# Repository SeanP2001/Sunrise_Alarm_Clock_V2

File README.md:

# Sunrise Alarm Clock V2

## Table of Contents

* [Introduction](#introduction)
* [Brief](#brief)
* [Method of Operation](#method-of-operation)
  + [Setup](#setup)
  + [Main Screen](#main-screen)
  + [Menu Layout](#menu-layout)
* [Circuitry](#circuitry)
  + [Schematic](#schematic)
  + [PCB Design](#pcb-design)
* [Enclosure](#enclosure)
  + [CAD Enclosure](#cad-enclosure)
  + [3D Printed Enclosure](#3d-printed-enclosure)
* [Demonstration](#demonstration)
* [Further Work](#further-work)

## Introduction

In my first year of university, I made a sunrise alarm clock for an assignment. Version 1 was a simple project using an Arduino Mega and an LCD keypad shield. [Here](https://github.com/SeanP2001/Arduino_Sunrise_Alarm_Clock) is a link to the repo for the original project. Over the past year and a half, I have developed my skills, so I decided to revisit this project.

## Brief

I wanted to design an alarm clock that uses light to wake me up naturally, making me feel more rested. However, I also needed an audio alarm to prevent me from solely relying on waking up naturally. Another feature I wanted to add was USB ports that could be switched on at time X and off at time Y. This would allow me to control USB-powered peripherals like lights, fans or a radio. I could also use these ports to charge devices without leaving them on charge all night.

## Method of Operation

### Setup

Before programming the alarm, you must put your Wi-Fi credentials in the "WifiCredentials.h" file.

```arduino
//------------------------ W I F I   C R E D E N T I A L S ------------------------

const char *ssid     = "YOUR_WIFI_SSID";        // REPLACE WITH YOUR WIFI SSID
const char *password = "YOUR_WIFI_PASSWORD";    // REPLACE WITH YOUR WIFI PASSWORD
```

When the alarm is first powered on, it will connect to your Wi-Fi to get the current date and time. It will then load any settings from EEPROM before it advances to the main screen (shown below).

### Main Screen

The alarm displays the day of the week and the current time on the main screen. There are also three icons. Unfortunately, the icons do not show up well in photos.

Pressing the left button will toggle the light bar on and off. When the light bar is on, the icon on the left (light bulb) changes to show it is on. When it is on, the bulb is shaded in, and when it is off, the icon is just an outline of a bulb. The light is a useful feature to help you see when you are getting into bed in the dark.

Pressing the middle button enables and disables the audio alarm. Pressing this button will cause the central icon (a bell) to change from being shaded in when the buzzer is enabled to an outline when it is disabled. If the alarm sounds, pressing the middle button will turn it off.

Pressing the right button enters the menu (shown below).

### Menu Layout

The menu has the following layout:

```
Main Menu
├── Alarm
│   ├── Light Bar
│   │   ├── On Time
│   │   └── Off Time
│   └── Buzzer
│       ├── On Time
│       └── Off Time
├── USB Ports
│   ├── USB 1
│   │   ├── On Time
│   │   └── Off Time
│   ├── USB 2
│   │   ├── On Time
│   │   └── Off Time
│   └── USB 3
│       ├── On Time
│       └── Off Time
├── Time
│   ├── Time Offset (hrs)
│   ├── Hours Between Syncs
│   └── Sync Time Now
└── Save
```

The "Alarm" settings allow you to alter when the light bar and buzzer automatically turn on and off. The "USB Ports" settings adjust when each port turns on and off.

In the "Time" menu, the "Time Offset" option allows you to set how many hours your time zone is ahead or behind UTC. The "Hours Between Syncs" option allows you to set how many hours the clock will run before it syncs to the time server again. "Sync Time Now" causes the alarm to reconnect to the Wi-Fi and connect to the time server to get the current time. This option is helpful if you have just altered the time offset and want to update the clock.

The "Save" option saves all of the settings to the EEPROM. This means you will not lose your settings when you turn the alarm off and back on again.

## Circuitry

### Schematic

### PCB Design

|  |  |
| -------------------------------------------------- | ------------------------------------------------------- |
|                |                      |

## Enclosure

### CAD Enclosure

|  |  |
| ---------------------------------------------------------------------- | ------------------------------------------------------------ |

### 3D Printed Enclosure

|  |  |  |
| ------------------------------------- | ------------------------------------------ | -------------------------------------- |

## Demonstration

## Further Work

In future, I could;

- Create other wireless modules with which the alarm can communicate (windowsill light sensor, curtain motor, lamp).
- Add a weather icon to the main screen.
- Change the design to a more traditional alarm clock shape.
- Add a puzzle to switch off the alarm. This would prevent you from just hitting snooze.

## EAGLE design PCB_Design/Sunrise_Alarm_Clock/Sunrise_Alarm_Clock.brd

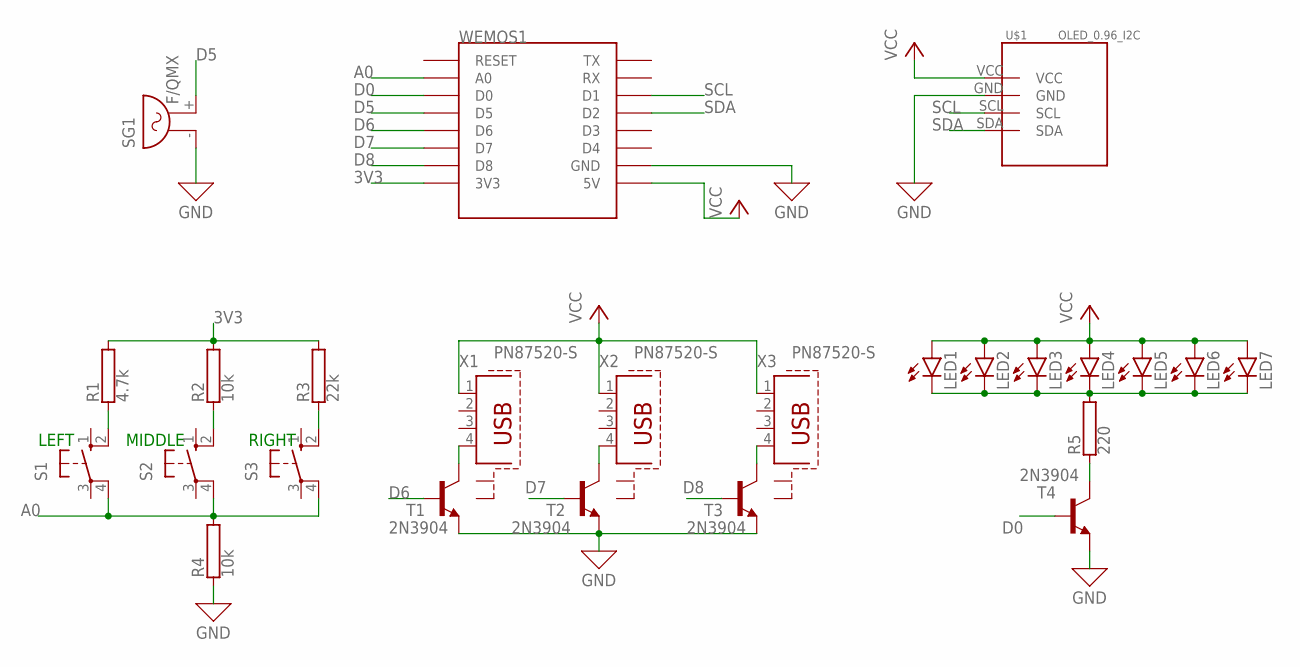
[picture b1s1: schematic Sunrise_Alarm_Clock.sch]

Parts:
LED1, LED2, LED3, LED4, LED5, LED6, LED7: LED5MM
R1: 4.7k; AC01
R2, R4: 10k; AC01
R3: 22k; AC01
R5: 220; AC01
S1, S2, S3: 10-XX; B3F-10XX
SG1: F/QMX
T1, T2, T3, T4: 2N3904; TO92
U$1: OLED_0.96_I2C
WEMOS1: WEMOS-D1-MINI
X1, X2, X3: PN87520-S

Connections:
3V3: R1.2, R2.2, R3.2, WEMOS1.3V3
A0: R4.2, S1.4 (P1), S2.4 (P1), S3.4 (P1), WEMOS1.A0
D0: T4.2 (B), WEMOS1.D0
D5: SG1.+ (2), WEMOS1.D5
D6: T1.2 (B), WEMOS1.D6
D7: T2.2 (B), WEMOS1.D7
D8: T3.2 (B), WEMOS1.D8
GND: R4.1, SG1.- (1), T1.3 (E), T2.3 (E), T3.3 (E), T4.3 (E), U$1.GND, WEMOS1.GND
unnamed: T3.1 (C), X3.4
unnamed: T2.1 (C), X2.4
unnamed: T1.1 (C), X1.4
unnamed: R3.1, S3.2 (S1)
unnamed: R2.1, S2.2 (S1)
unnamed: R1.1, S1.2 (S1)
unnamed: R5.1, T4.1 (C)
unnamed: LED1.K (C), LED2.K (C), LED3.K (C), LED4.K (C), LED5.K (C), LED6.K (C), LED7.K (C), R5.2
SCL: U$1.SCL, WEMOS1.D1
SDA: U$1.SDA, WEMOS1.D2
VCC: LED1.A, LED2.A, LED3.A, LED4.A, LED5.A, LED6.A, LED7.A, U$1.VCC, WEMOS1.5V, X1.1, X2.1, X3.1

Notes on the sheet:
LEFT
MIDDLE
RIGHT

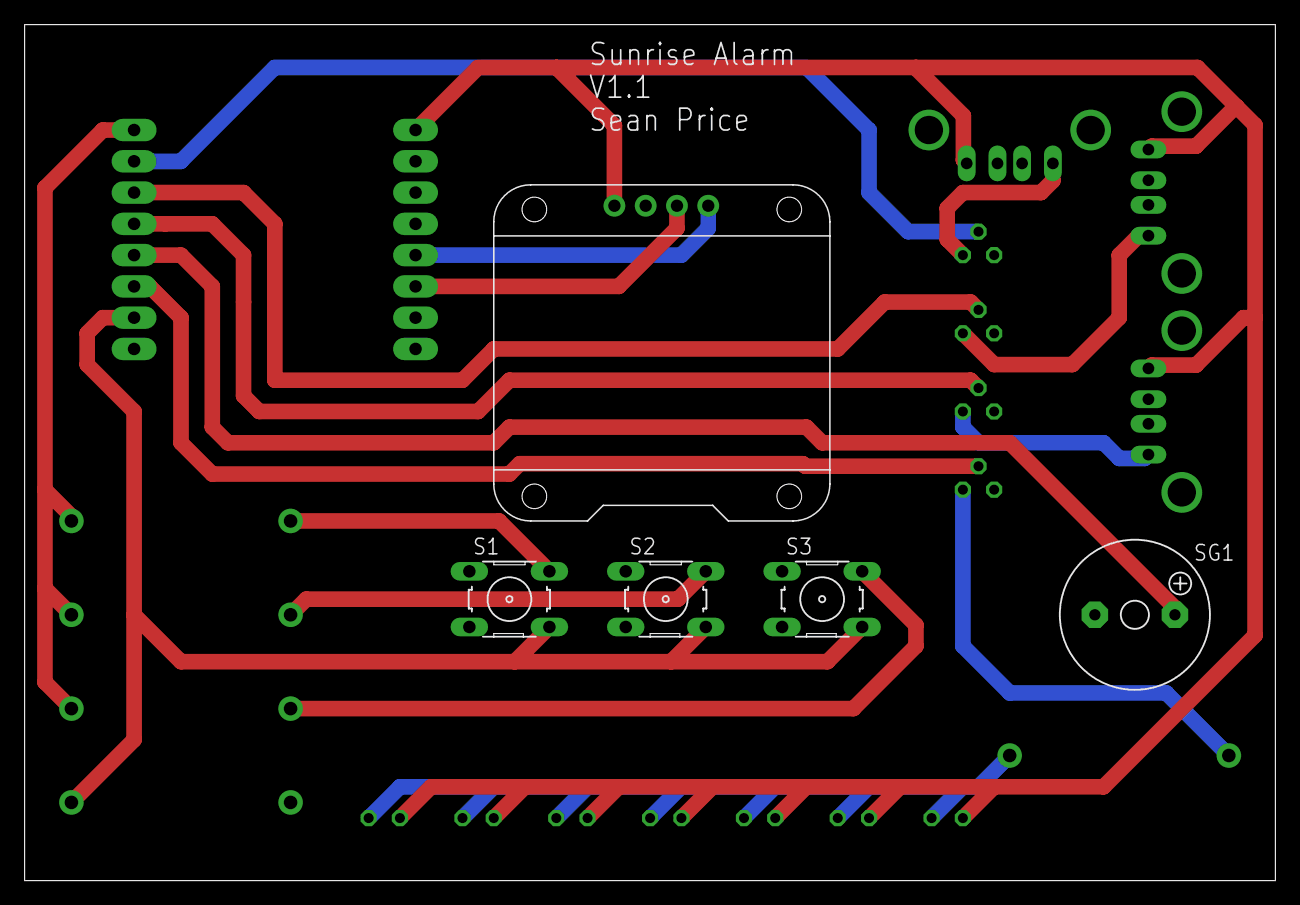
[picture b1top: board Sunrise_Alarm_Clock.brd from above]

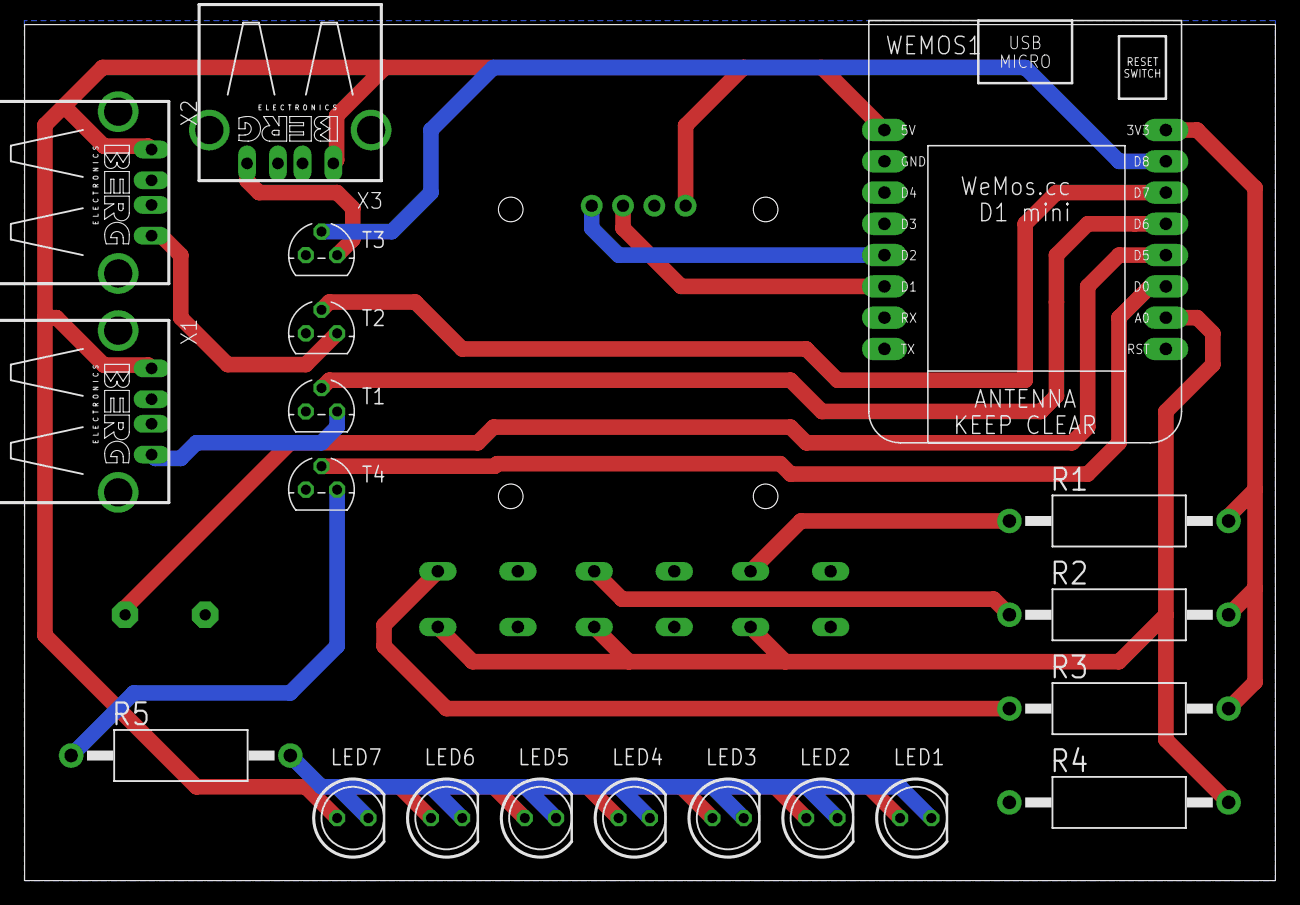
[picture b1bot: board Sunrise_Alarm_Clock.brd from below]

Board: 2 copper layers, 101.6 x 69.5 mm, 25 parts (20 on the bottom side), 19 nets.

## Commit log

2022-03-23 V2.1.0-alpha Added PCB design files
2022-05-28 V2.1.1-alpha PCB V1.1
    - Placed LEDs, USBs and D1 mini on the rear of the board
    - Changed USB footprint to include shield pads
    - Fixed transistors to be common-emitter
    - Broke schematic into sections to make it easier to follow
    - Hand-routed thicker traces
2022-05-29 V2.1.2-alpha Generated gerber files showing silkscreen component values
2022-06-07 V2.1.3-alpha Finalised PCB V1.1
2022-08-23 V2.2.0-alpha Created a 3D Model of the populated PCB
2022-08-23 V2.2.1-alpha Designed an Enclosure
2022-08-23 V2.2.2-alpha Fixed a Typo
2022-09-03 V2.2.3-alpha Modified the Enclosure to be Stronger
2022-09-03 V2.2.4-alpha Separated the Parts in the Printable File
2022-09-06 V2.3.0-alpha Programmed a Clock Which NTP Syncs Every 12 Hours
2022-09-06 V2.3.1-alpha Added a WiFi connection timeout
2022-09-06 V2.3.2-alpha Changed the daysOfTheWeek Array to Start on Monday
2022-09-06 V2.3.3-alpha Declared all of the IO Pins
2022-09-06 V2.4.0-alpha Added the Button Class and Added Night Light Functionality
2022-09-08 V2.5.0-alpha Added the Menu System
2022-09-09 V2.5.1-alpha Re-organised Menu Selecting to Allow for Adjusting Settings
2022-09-09 V2.5.2-alpha Added Functionality to all of the Settings
2022-09-09 V2.6.0-alpha Made all IO Operational
2022-09-10 V2.6.1-alpha Added Icons and Updated the Graphics
2022-09-10 V2.6.2-alpha Added screen timeout
2022-09-10 V2.6.3-alpha Reorganised Code
2022-09-10 V2.7.0-alpha Added Loading and Saving Settings
2022-09-12 V2.7.1-alpha Fixed Bug Preventing Automatic Screen Timeout
    Previously the screen would not turn off at night unless you pressed a button. It would then timeout 1 minute later. The screen also did not turn back on in the morning without pressing a button.
    Now the screen will automatically turn off at 10PM and turn back on at 7AM. During this period pressing a button will turn the screen back on before it times out a minute later.
2022-09-12 V2.7.2-alpha Fixed Bug Preventing Outputs Turning On During Night Hours
    Previously none of the outputs could be turned on or off automatically during the night hours (22:00-07:00). This meant that if you set the light bar to turn on at 6AM, it would not turn on unless yo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
    Now all of the outputs can be switched on and off regardless of the time of day or whether the screen is on or off.
2022-09-12 V2.7.3-alpha Temporarily Fixed Bug Causing Weekday to Glitch
    Previously the alarm would show the day of the week but when it changed from Saturday to Sunday the screen would glitch and the day of the week would not be displayed.
    I found that this was because I was using the day() function instead of the weekday() function. The day function actually returns the day of the month and not the day of the week. As a result it was 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
    To fix this I changed from using the day() function to using the weekday() function. However, this takes into consideration the month and year. Unfortunately I cannot get the month and year using the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
2022-09-12 V2.7.4-alpha Fixed Bug Causing Weekday to Glitch
    I have switched to using a different NTPClient library (included). This library includes the getFormattedDate() function. Using this function I was able to extract the day, month and year which I cou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
2022-09-13 V2.7.5-alpha Updated README.md
2022-09-13 V2.7.6-alpha Updated README.md
2022-09-13 V2.7.7-alpha Updated README.md
2022-09-13 V2.7.8-alpha Updated README.md
2022-09-13 V2.7.9-alpha Updated README.md
2022-09-13 V2.7.10-alpha Updated README.md
2022-09-14 V2.0.0-release Updated README.md
2022-09-14 V2.0.1-release Added LICENSE.md
2023-08-18 V2.0.2-release Fixed Issue #1: Menu Crash and Memory Usage
    Description:
    It was suspected that the dynamic creation of MenuItem objects was causing the microcontroller to run out of memory and subsequently crash. This issue has been addressed with this update.
    Changes Made:
    - Removed the MenuItem class
    - Removed the Menu class
    - Introduced the MenuItem struct
2023-08-21 V2.0.3-release Split Code Into DisplayManager & SettingsManager
2023-08-26 V2.0.4-release Added the Device Class
2023-08-27 V2.0.5-release Moved WiFi Credentials
2023-08-27 V2.0.6-release Updated gitignore
2023-08-27 V2.0.7-release: Improved Code Readability
    In this release, the readability, modularity, and maintainability of the code have been improved through the following changes:
    - **Enhanced Function Portability and Encapsulation:** Arguments have been introduced to several functions to improve their portability and encapsulation. The affected functions include `itIsNight`, 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
    - **Code Reusability:** To eliminate redundant code segments, new functions were introduced. Notably, the `displayBlankScreen` and `resetScreenTimeout` functions were created.
    - **Refactored Display-Related Functions:** Display-related functions such as `displayBlankScr
2023-08-28 V2.0.8-release: Added Device Subclasses
    Separated device behaviour into distinct classes: Device, Alarm, USB, and Light.
    - The Device class handles common functionality such as setting on/off times and checking whether the device should be on or off at a given time.
    - The Alarm class extends Device for alarm-specific features: enable/disable, sounding, and output management.
    - The USB and Light classes inherit from Device, each focusing on their unique behaviours.
    This restructuring enhances code organisation, modularity, and readability.
2023-08-29 V2.0.9-release Fixed Issue #2: On/Off Time Logic
    Previously the logic in `Device::itIsOnTime()` could not handle situations where the device needed to turn on in the evening, and off in the morning (like a phone charging). This was because "onTime 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
    Now `Device::itIsOnTime()` has been updated to check whether "onTime > offTime", and if so, check if it is either after the on time at night, or before the off time in the morning.
    Resolves: #2
